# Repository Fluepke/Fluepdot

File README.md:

# Fluepdot

**Fluepdot** is a hardware and C project for controlling flip disc panels which where in use by the Berlin public transport operator **[BVG](https://www.bvg.de/en)**.

> This project was shown at [36C3](https://events.ccc.de/congress/2019/wiki/index.php/Main_Page). A large display was constructed from many flipdots. [Pictures](https://www.deutschlandfunkkultur.de/chaos-communication-congress-in-leipzig-auf-den-spuren-von.1264.de.html?dram:article_id=466775) [of](https://foto.benedikt-geyer.de/fluepdot-36c3/) [the](https://www.korrupt.biz/7204/36c3-nachtraege/) [installation](https://www.astrastudio.de/cloud/index.php/apps/gallery/s/nDda9j8dZQ2oNMy#IMG_7059.jpeg).

## Documentation
For **documentation** and a **getting started**, please head over to [https://fluepdot.readthedocs.io/en/latest/](https://fluepdot.readthedocs.io/en/latest/).

## Hardware

Flipdots and required HW  can be purchased by contacting [fluepdot-sales@luepke.email](mailto:fluepdot-sales@luepke.email).

## Firmware
You can download the latest standalone firmware installer [here](https://gitlab.com/fluepke/fluepdot/-/jobs/artifacts/master/raw/software/service_utility/service_utility?job=build_service_utility).

## License
Copyright (c) 2020, [@fluepke](http://twitter.com/fluepke) (Fabian Luepke)

Distributed under the terms of the GNU Affero General Public License version 3.

The full license is in the file LICENSE, distributed with this software.

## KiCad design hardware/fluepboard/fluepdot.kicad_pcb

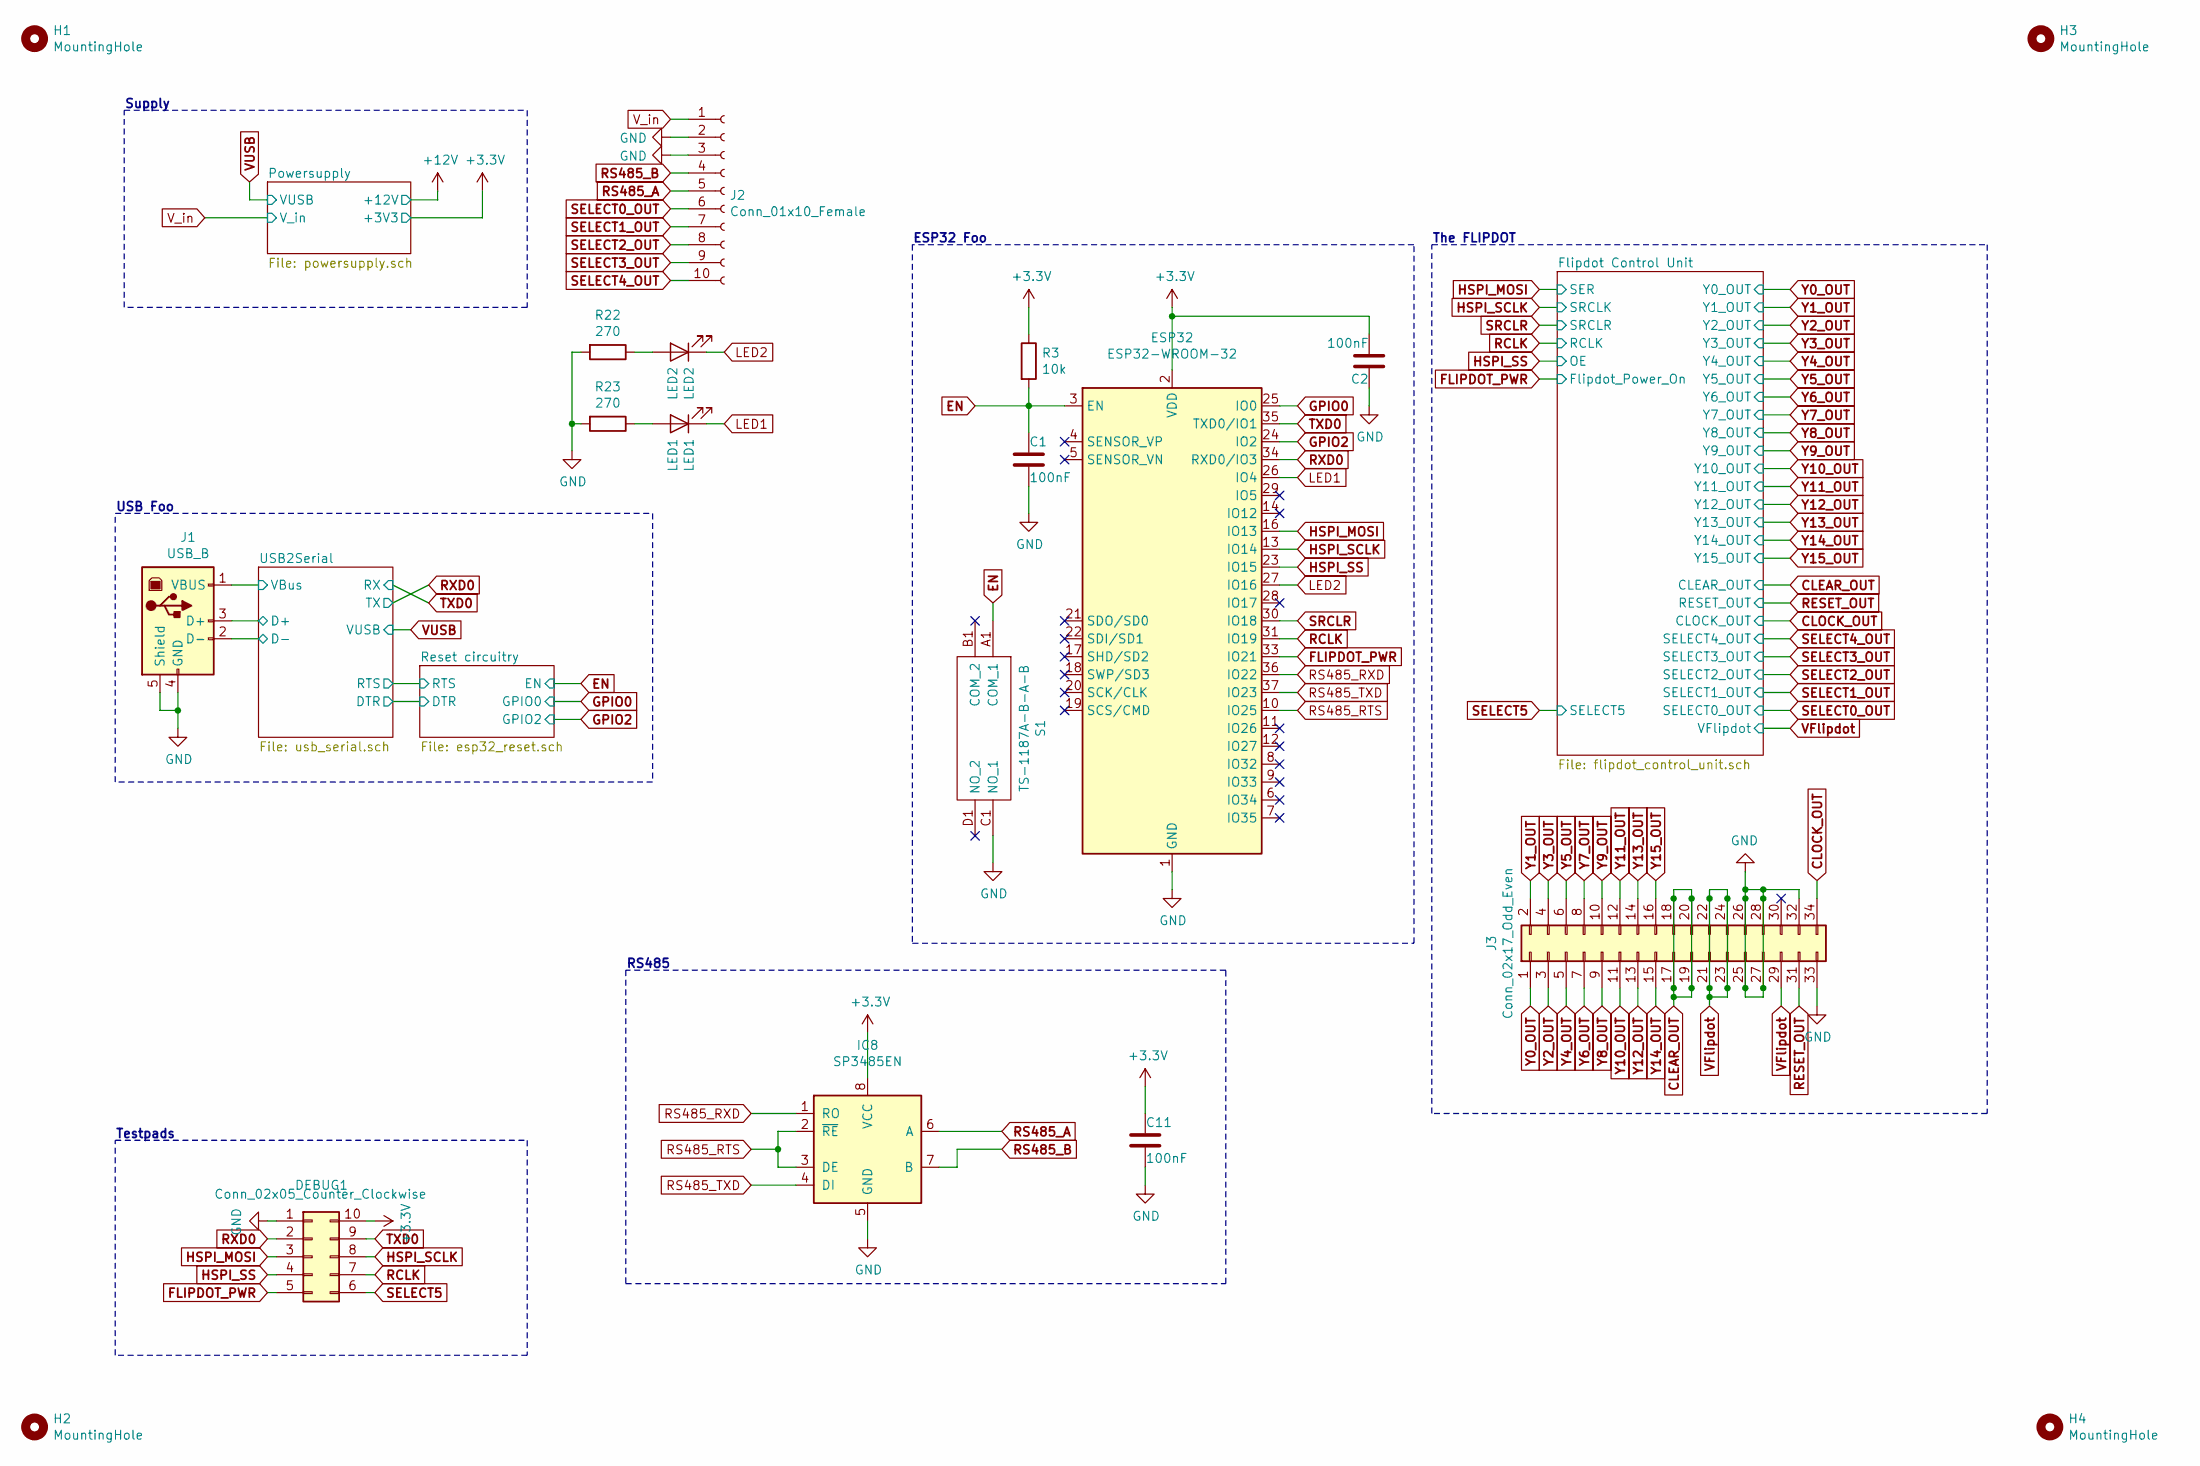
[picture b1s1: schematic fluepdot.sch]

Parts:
C1, C2, C11: 100nF; C_0603_1608Metric; LCSC C14663
DEBUG1: Conn_02x05_Counter_Clockwise; PinHeader_2x05_P2.54mm_Vertical
ESP32: ESP32-WROOM-32
H1, H2, H3, H4: MountingHole; MountingHole_3.2mm_M3_ISO7380
IC8: SP3485EN; SOIC-8_3.9x4.9mm_P1.27mm; LCSC C8963
J1: USB_B; USB_B_OST_USB-B1HSxx_Horizontal; LCSC C46392
J2: Conn_01x10_Female; TerminalBlock_Phoenix_MPT-0,5-10-2.54_1x10_P2.54mm_Horizont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
J3: Conn_02x17_Odd_Even; PinHeader_2x17_P2.54mm_Vertical
LED1: LED1; D_0805_2012Metric; LCSC C2296
LED2: LED2; D_0805_2012Metric; LCSC C2296
R3: 10k; R_0603_1608Metric; LCSC C25804
R22, R23: 270; R_0603_1608Metric; LCSC C22966
S1: TS-1187A-B-A-B; TS1187ABAB; Manufacturer_Part_Number TS-1187A-B-A-B; LCSC C318884

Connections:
+3V3: C2.2, C11.1, DEBUG1.10, ESP32.2 (VDD), IC8.8 (VCC), R3.1; also elsewhere on the board
/USB2Serial/D+: J1.3 (D+); also elsewhere on the board
/USB2Serial/D-: J1.2 (D-); also elsewhere on the board
/USB2Serial/VBus: J1.1 (VBUS); also elsewhere on the board
CLEAR_OUT: J3.17, J3.18, J3.19, J3.20; also elsewhere on the board
CLOCK_OUT: J3.34; also elsewhere on the board
EN: C1.1, ESP32.3 (EN), R3.2, S1.A1 (COM_1); also elsewhere on the board
FLIPDOT_PWR: DEBUG1.5, ESP32.33 (IO21); also elsewhere on the board
GND: C1.2, C2.1, C11.2, DEBUG1.1, ESP32.1 (GND), ESP32.15 (GND), ESP32.38 (GND), IC8.5 (GND), J1.4 (GND), J1.5 (Shield), J2.2, J2.3, J3.25, J3.26, J3.27, J3.28, J3.32, J3.33, R22.2, R23.2, S1.C1 (NO_1); also elsewhere on the board
GPIO0: ESP32.25 (IO0); also elsewhere on the board
GPIO2: ESP32.24 (IO2); also elsewhere on the board
HSPI_MOSI: DEBUG1.3, ESP32.16 (IO13); also elsewhere on the board
HSPI_SCLK: DEBUG1.8, ESP32.13 (IO14); also elsewhere on the board
HSPI_SS: DEBUG1.4, ESP32.23 (IO15); also elsewhere on the board
LED1: ESP32.26 (IO4), LED1.1 (K)
LED2: ESP32.27 (IO16), LED2.1 (K)
unnamed: LED1.2 (A), R23.1
unnamed: LED2.2 (A), R22.1
RCLK: DEBUG1.7, ESP32.31 (IO19); also elsewhere on the board
RESET_OUT: J3.31; also elsewhere on the board
RS485_A: IC8.6 (A), J2.5
RS485_B: IC8.7 (B), J2.4
RS485_RTS: ESP32.10 (IO25), IC8.2 (~RE~), IC8.3 (DE)
RS485_RXD: ESP32.36 (IO22), IC8.1 (RO)
RS485_TXD: ESP32.37 (IO23), IC8.4 (DI)
RXD0: DEBUG1.2, ESP32.34 (RXD0/IO3); also elsewhere on the board
SELECT0_OUT: J2.6; also elsewhere on the board
SELECT1_OUT: J2.7; also elsewhere on the board
SELECT2_OUT: J2.8; also elsewhere on the board
SELECT3_OUT: J2.9; also elsewhere on the board
SELECT4_OUT: J2.10; also elsewhere on the board
SELECT5: DEBUG1.6; also elsewhere on the board
SRCLR: ESP32.30 (IO18); also elsewhere on the board
TXD0: DEBUG1.9, ESP32.35 (TXD0/IO1); also elsewhere on the board
VFlipdot: J3.21, J3.22, J3.23, J3.24, J3.29; also elsewhere on the board
V_in: J2.1; also elsewhere on the board
Y0_OUT: J3.1; also elsewhere on the board
Y1_OUT: J3.2; also elsewhere on the board
Y2_OUT: J3.3; also elsewhere on the board
Y3_OUT: J3.4; also elsewhere on the board
Y4_OUT: J3.5; also elsewhere on the board
Y5_OUT: J3.6; also elsewhere on the board
Y6_OUT: J3.7; also elsewhere on the board
Y7_OUT: J3.8; also elsewhere on the board
Y8_OUT: J3.9; also elsewhere on the board
Y9_OUT: J3.10; also elsewhere on the board
Y10_OUT: J3.11; also elsewhere on the board
Y11_OUT: J3.12; also elsewhere on the board
Y12_OUT: J3.13; also elsewhere on the board
Y13_OUT: J3.14; also elsewhere on the board
Y14_OUT: J3.15; also elsewhere on the board
Y15_OUT: J3.16; also elsewhere on the board

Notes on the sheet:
Testpads
USB Foo
Supply
ESP32 Foo
The FLIPDOT
RS485

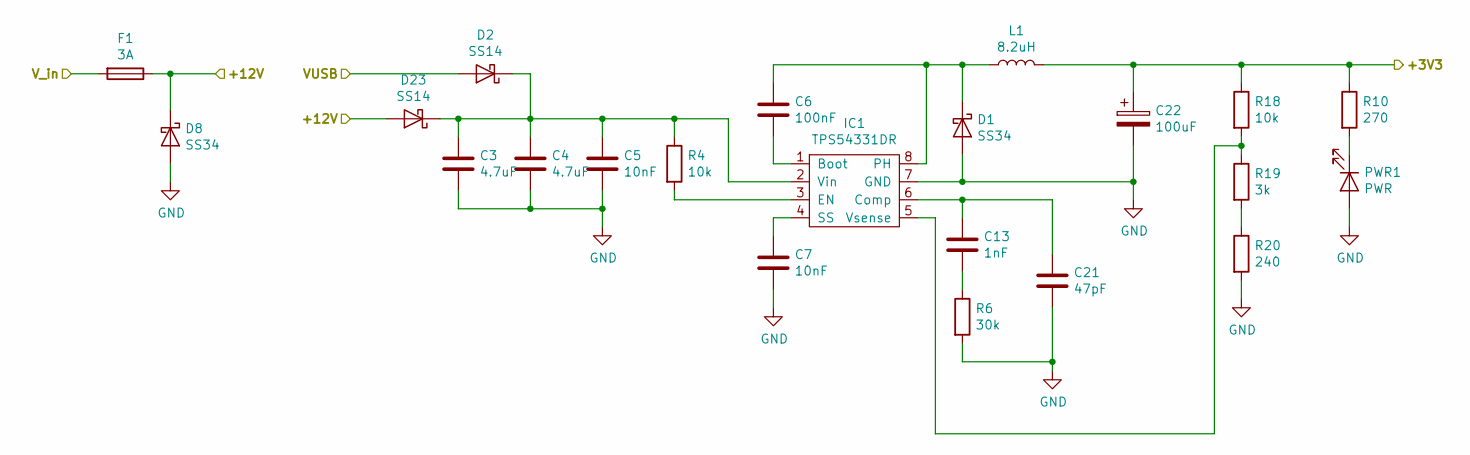
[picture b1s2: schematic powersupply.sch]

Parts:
C3, C4: 4.7uF; C_0805_2012Metric; LCSC C1779
C5, C7: 10nF; C_0603_1608Metric; LCSC C57112
C6: 100nF; C_0603_1608Metric; LCSC C14663
C13: 1nF; C_0603_1608Metric; LCSC C1588
C21: 47pF; C_0603_1608Metric; LCSC C1671
C22: 100uF; CP_EIA-3528-21_Kemet-B; LCSC C16133
D1, D8: SS34; D_SMA; LCSC C84635
D2, D23: SS14; D_SMA; LCSC C2480
F1: 3A; Fuse_1206_3216Metric; LCSC C182441
IC1: TPS54331DR; SOIC-8_3.9x4.9mm_P1.27mm; LCSC C9865
L1: 8.2uH; SMD-PIND-6.6x7.1x3.0_1.6x3.0; LCSC C132140
PWR1: PWR; D_0805_2012Metric; LCSC C2296
R4, R18: 10k; R_0603_1608Metric; LCSC C25804
R6: 30k; R_0603_1608Metric; LCSC C22984
R10: 270; R_0603_1608Metric; LCSC C22966
R19: 3k; R_0603_1608Metric; LCSC C4211
R20: 240; R_0603_1608Metric; LCSC C23350

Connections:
+3V3: C22.1, L1.2, R10.1, R18.1; also elsewhere on the board
+12V: D8.1 (K), D23.2 (A), F1.1; also elsewhere on the board
GND: C3.2, C4.2, C5.2, C7.2, C21.2, C22.2, D1.2 (A), D8.2 (A), IC1.7 (GND), PWR1.2 (A), R6.2, R20.2; also elsewhere on the board
unnamed: C3.1, C4.1, C5.1, D2.1 (K), D23.1 (K), IC1.2 (Vin), R4.1
unnamed: C6.1, D1.1 (K), IC1.8 (PH), L1.1
unnamed: C6.2, IC1.1 (Boot)
unnamed: C7.1, IC1.4 (SS)
unnamed: C13.1, C21.1, IC1.6 (Comp)
unnamed: C13.2, R6.1
unnamed: IC1.3 (EN), R4.2
unnamed: IC1.5 (Vsense), R18.2, R19.1
unnamed: PWR1.1 (K), R10.2
unnamed: R19.2, R20.1
VUSB: D2.2 (A); also elsewhere on the board
V_in: F1.2; also elsewhere on the board

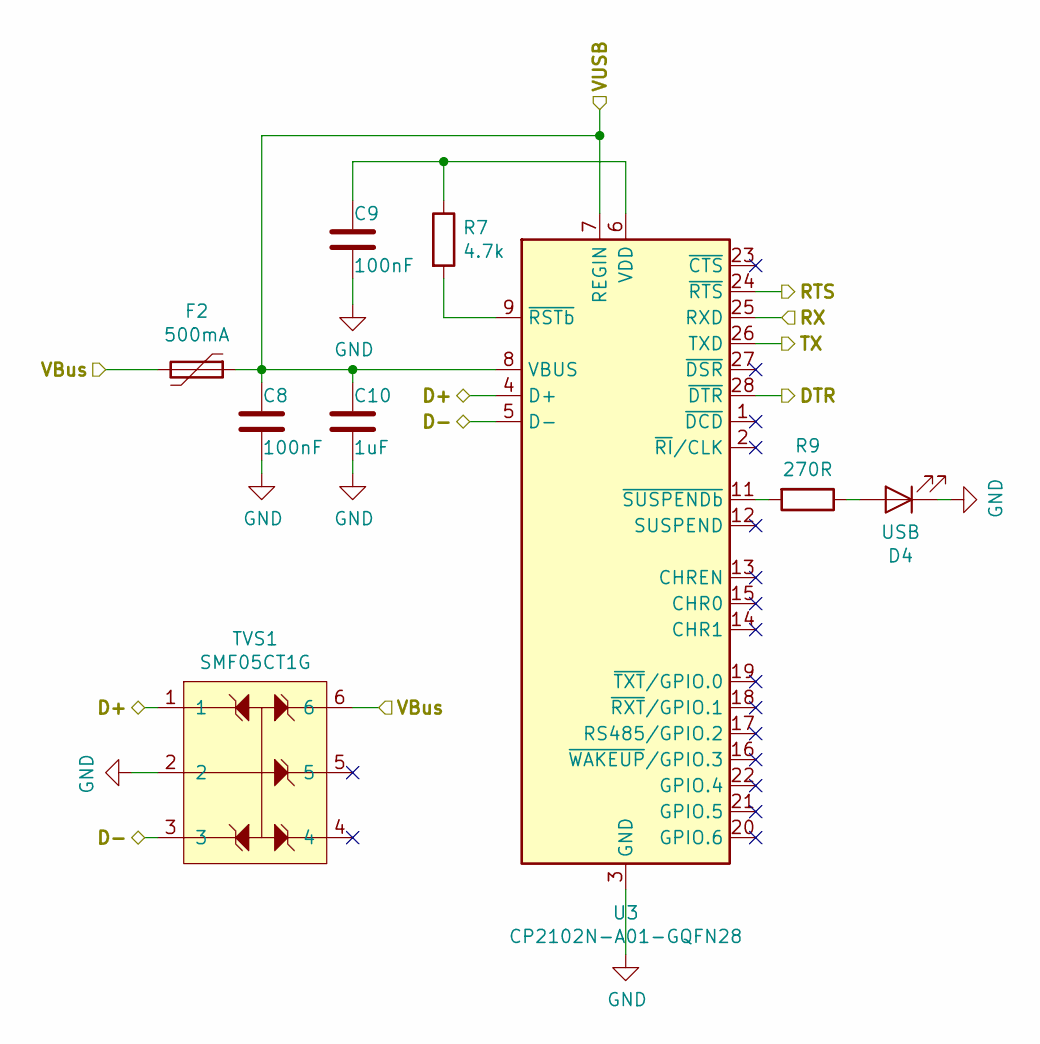
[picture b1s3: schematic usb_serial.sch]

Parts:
C8, C9: 100nF; C_0603_1608Metric; LCSC C14663
C10: 1uF; C_0603_1608Metric; LCSC C15849
D4: USB; D_0805_2012Metric; LCSC C2296
F2: 500mA; Fuse_1206_3216Metric; LCSC C69688
R7: 4.7k; R_0603_1608Metric; LCSC C23162
R9: 270R; R_0603_1608Metric; LCSC C22966
TVS1: SMF05CT1G; SOT-363_SC-70-6; LCSC C15879
U3: CP2102N-A01-GQFN28; QFN-28-1EP_5x5mm_P0.5mm_EP3.35x3.35mm; LCSC C6568

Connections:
/Reset circuitry/DTR: U3.28 (~DTR); also elsewhere on the board
/Reset circuitry/RTS: U3.24 (~RTS); also elsewhere on the board
/USB2Serial/D+: TVS1.1, U3.4 (D+); also elsewhere on the board
/USB2Serial/D-: TVS1.3, U3.5 (D-); also elsewhere on the board
/USB2Serial/VBus: F2.2, TVS1.6; also elsewhere on the board
GND: C8.1, C9.1, C10.1, D4.1 (K), TVS1.2, U3.3 (GND), U3.29 (GND); also elsewhere on the board
unnamed: C9.2, R7.1, U3.6 (VDD)
unnamed: D4.2 (A), R9.1
unnamed: R7.2, U3.9 (~RSTb)
unnamed: R9.2, U3.11 (~SUSPENDb)
RXD0: U3.26 (TXD); also elsewhere on the board
TXD0: U3.25 (RXD); also elsewhere on the board
VUSB: C8.2, C10.2, F2.1, U3.7 (REGIN), U3.8 (VBUS); also elsewhere on the board

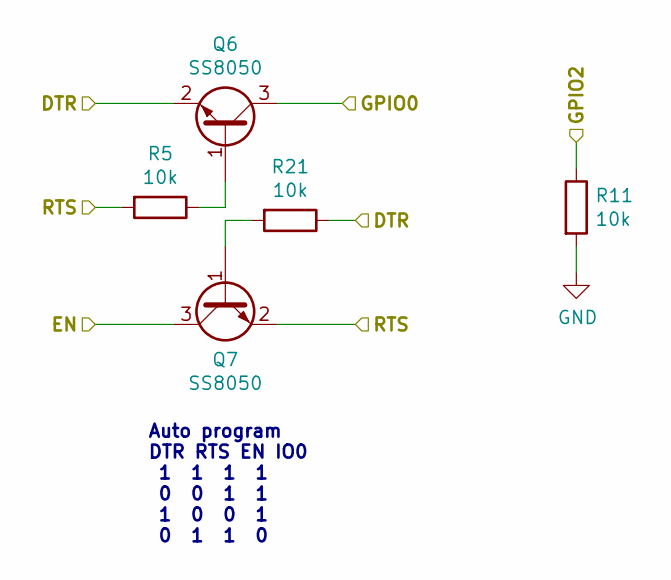
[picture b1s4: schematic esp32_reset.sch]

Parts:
Q6, Q7: SS8050; SOT-23; LCSC C2150
R5, R11, R21: 10k; R_0603_1608Metric; LCSC C25804

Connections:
/Reset circuitry/DTR: Q6.2 (E), R21.1; also elsewhere on the board
/Reset circuitry/RTS: Q7.2 (E), R5.2; also elsewhere on the board
EN: Q7.3 (C); also elsewhere on the board
GND: R11.2; also elsewhere on the board
GPIO0: Q6.3 (C); also elsewhere on the board
GPIO2: R11.1; also elsewhere on the board
unnamed: Q6.1 (B), R5.1
unnamed: Q7.1 (B), R21.2

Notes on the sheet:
Auto program DTR RTS EN IO0 1 1 1 1 0 0 1 1 1 0 0 1 0 1 1 0

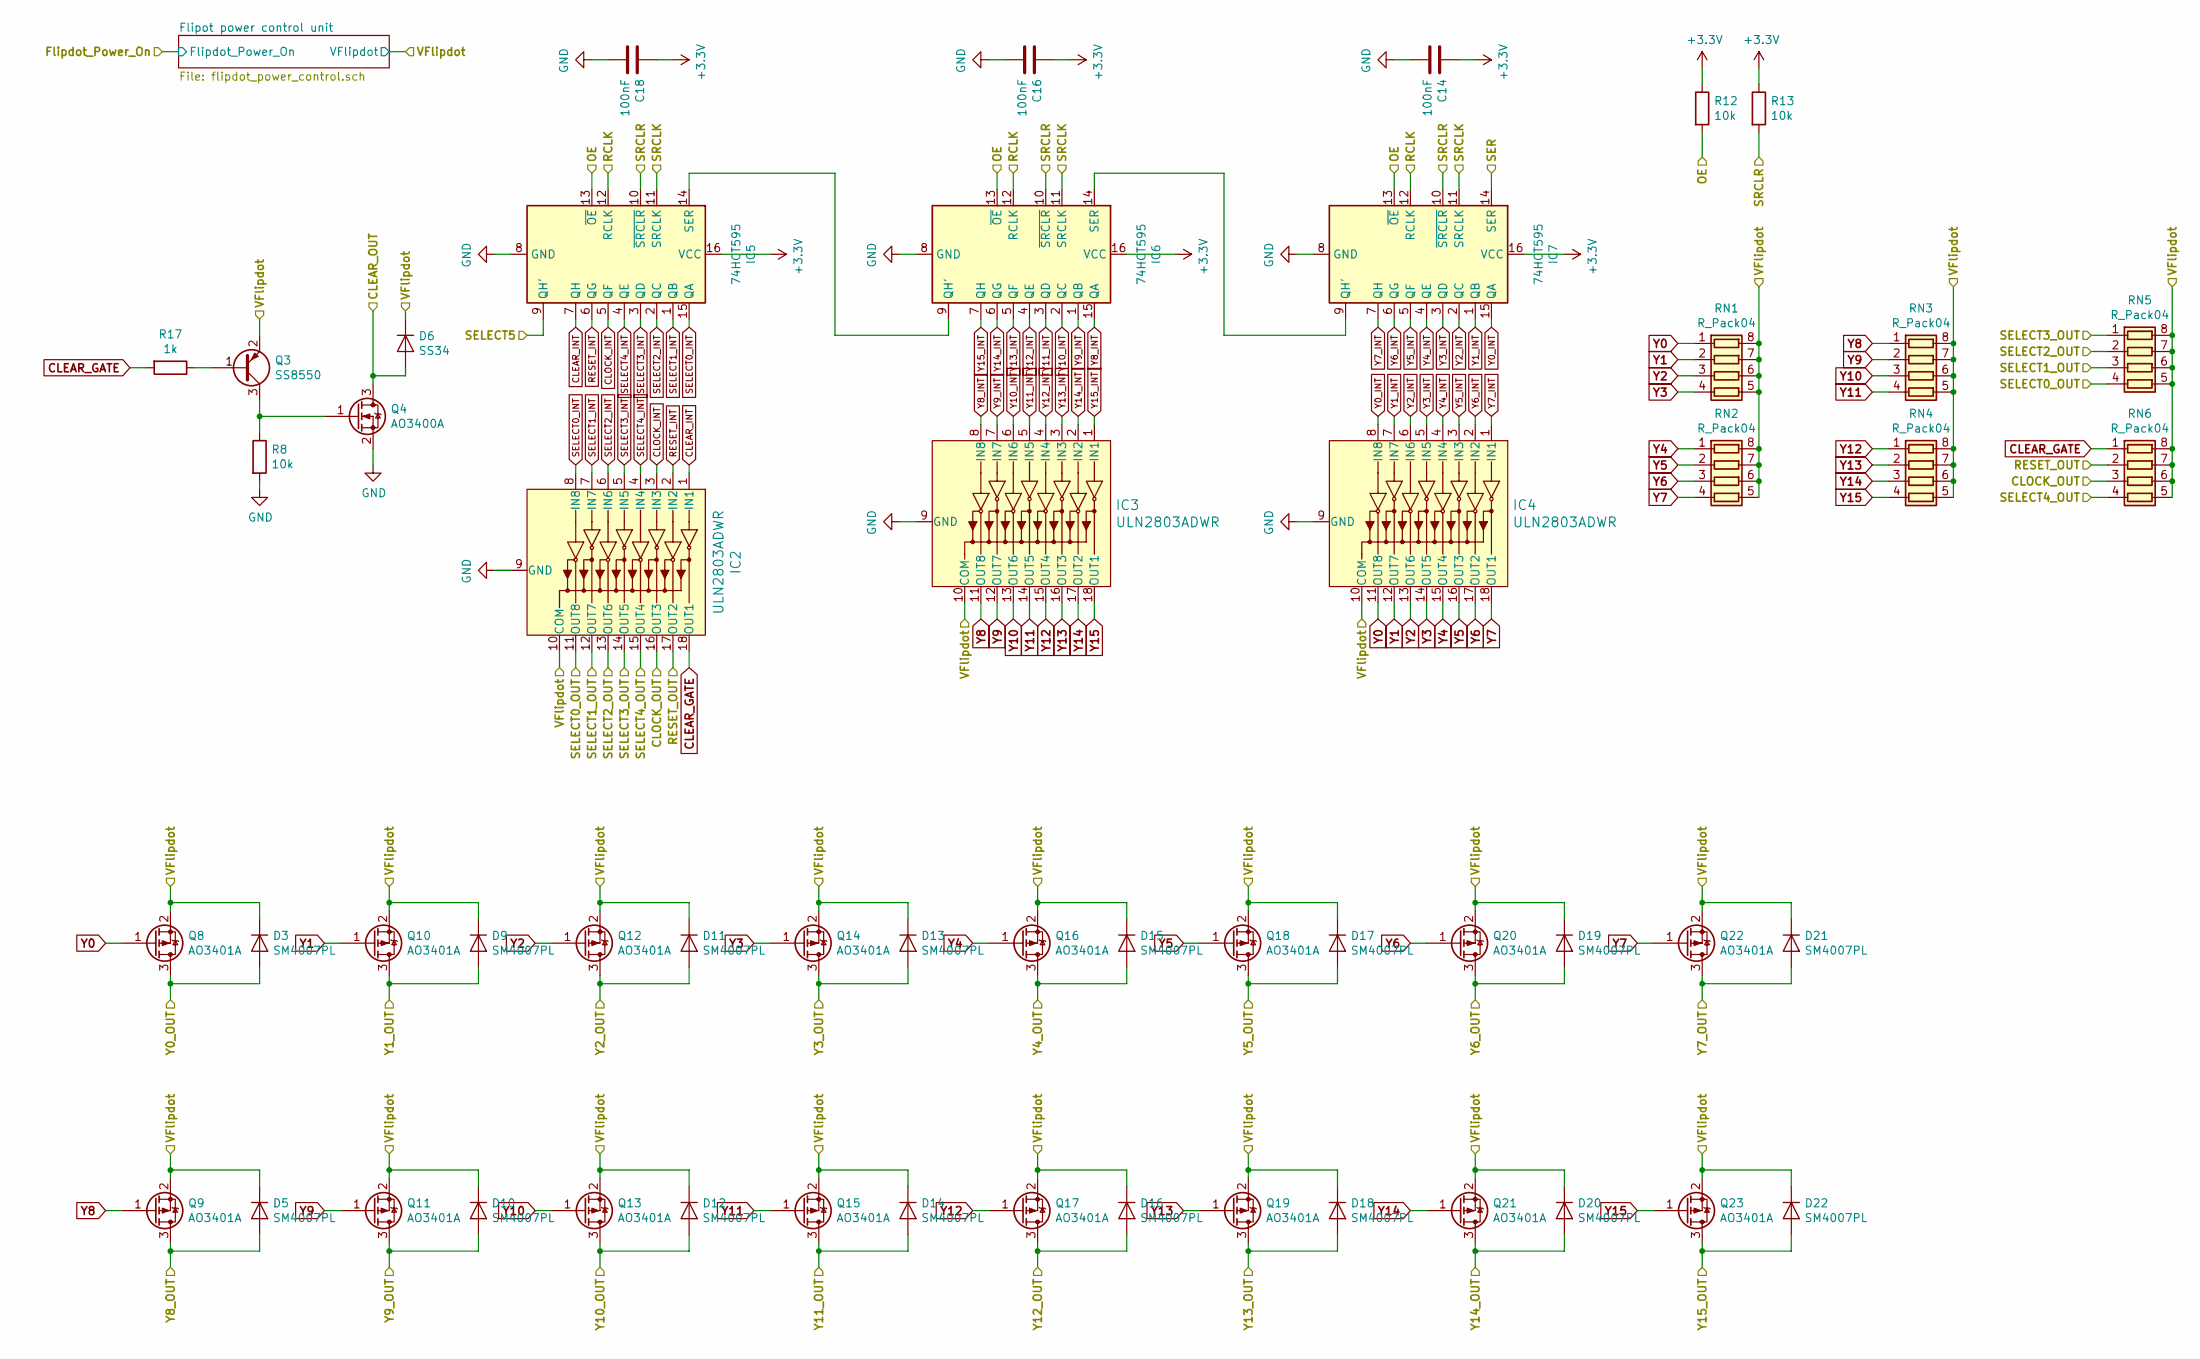
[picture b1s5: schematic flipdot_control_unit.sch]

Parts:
C14, C16, C18: 100nF; C_0603_1608Metric; LCSC C14663
D3, D5, D9, D10, D11, D12, D13, D14, D15, D16, D17, D18, D19, D20, D21, D22: SM4007PL; D_SOD-123F; LCSC C64898
D6: SS34; D_SMA; LCSC C84635
IC2, IC3, IC4: ULN2803ADWR; SOIC-18W_7.5x11.6mm_P1.27mm; MPN ULN2803ADWR; Digi-Key_PN 296-15777-1-ND
IC5, IC6, IC7: 74HCT595; SOIC-16_3.9x9.9mm_P1.27mm; LCSC C5613
Q3: SS8550; SOT-23; LCSC C8542
Q4: AO3400A; SOT-23; LCSC C20917
Q8, Q9, Q10, Q11, Q12, Q13, Q14, Q15, Q16, Q17, Q18, Q19, Q20, Q21, Q22, Q23: AO3401A; SOT-23; LCSC C15127
R8, R12, R13: 10k; R_0603_1608Metric; LCSC C25804
R17: 1k; R_0603_1608Metric; LCSC C21190
RN1, RN2, RN3, RN4, RN5, RN6: R_Pack04; R_Array_Convex_4x0603; LCSC C29718

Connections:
+3V3: C14.1, C16.1, C18.1, IC5.16 (VCC), IC6.16 (VCC), IC7.16 (VCC), R12.1, R13.1; also elsewhere on the board
CLEAR_GATE: IC2.18 (OUT1), R17.2, RN6.1 (R1.1)
CLEAR_INT: IC2.1 (IN1), IC5.7 (QH)
CLEAR_OUT: D6.2 (A), Q4.3 (D); also elsewhere on the board
CLOCK_INT: IC2.3 (IN3), IC5.5 (QF)
CLOCK_OUT: IC2.16 (OUT3), RN6.3 (R3.1); also elsewhere on the board
GND: C14.2, C16.2, C18.2, IC2.9 (GND), IC3.9 (GND), IC4.9 (GND), IC5.8 (GND), IC6.8 (GND), IC7.8 (GND), Q4.2 (S), R8.2; also elsewhere on the board
HSPI_MOSI: IC7.14 (SER); also elsewhere on the board
HSPI_SCLK: IC5.11 (SRCLK), IC6.11 (SRCLK), IC7.11 (SRCLK); also elsewhere on the board
HSPI_SS: IC5.13 (~OE), IC6.13 (~OE), IC7.13 (~OE), R12.2; also elsewhere on the board
unnamed: IC5.14 (SER), IC6.9 (QH')
unnamed: IC6.14 (SER), IC7.9 (QH')
unnamed: Q3.1 (B), R17.1
unnamed: Q3.3 (C), Q4.1 (G), R8.1
RCLK: IC5.12 (RCLK), IC6.12 (RCLK), IC7.12 (RCLK); also elsewhere on the board
RESET_INT: IC2.2 (IN2), IC5.6 (QG)
RESET_OUT: IC2.17 (OUT2), RN6.2 (R2.1); also elsewhere on the board
SELECT0_INT: IC2.8 (IN8), IC5.15 (QA)
SELECT0_OUT: IC2.11 (OUT8), RN5.4 (R4.1); also elsewhere on the board
SELECT1_INT: IC2.7 (IN7), IC5.1 (QB)
SELECT1_OUT: IC2.12 (OUT7), RN5.3 (R3.1); also elsewhere on the board
SELECT2_INT: IC2.6 (IN6), IC5.2 (QC)
SELECT2_OUT: IC2.13 (OUT6), RN5.2 (R2.1); also elsewhere on the board
SELECT3_INT: IC2.5 (IN5), IC5.3 (QD)
SELECT3_OUT: IC2.14 (OUT5), RN5.1 (R1.1); also elsewhere on the board
SELECT4_INT: IC2.4 (IN4), IC5.4 (QE)
SELECT4_OUT: IC2.15 (OUT4), RN6.4 (R4.1); also elsewhere on the board
SELECT5: IC5.9 (QH'); also elsewhere on the board
SRCLR: IC5.10 (~SRCLR), IC6.10 (~SRCLR), IC7.10 (~SRCLR), R13.2; also elsewhere on the board
VFlipdot: D3.1 (K), D5.1 (K), D6.1 (K), D9.1 (K), D10.1 (K), D11.1 (K), D12.1 (K), D13.1 (K), D14.1 (K), D15.1 (K), D16.1 (K), D17.1 (K), D18.1 (K), D19.1 (K), D20.1 (K), D21.1 (K), D22.1 (K), IC2.10 (COM), IC3.10 (COM), IC4.10 (COM), Q3.2 (E), Q8.2 (S), Q9.2 (S), Q10.2 (S), Q11.2 (S), Q12.2 (S), Q13.2 (S), Q14.2 (S), Q15.2 (S), Q16.2 (S), Q17.2 (S), Q18.2 (S), Q19.2 (S), Q20.2 (S), Q21.2 (S), Q22.2 (S), Q23.2 (S), RN1.5 (R4.2), RN1.6 (R3.2), RN1.7 (R2.2), RN1.8 (R1.2), RN2.5 (R4.2), RN2.6 (R3.2), RN2.7 (R2.2), RN2.8 (R1.2), RN3.5 (R4.2), RN3.6 (R3.2), RN3.7 (R2.2), RN3.8 (R1.2), RN4.5 (R4.2), RN4.6 (R3.2), RN4.7 (R2.2), RN4.8 (R1.2), RN5.5 (R4.2), RN5.6 (R3.2), RN5.7 (R2.2), RN5.8 (R1.2), RN6.5 (R4.2), RN6.6 (R3.2), RN6.7 (R2.2), RN6.8 (R1.2); also elsewhere on the board
Y0: IC4.11 (OUT8), Q8.1 (G), RN1.1 (R1.1)
Y0_INT: IC4.8 (IN8), IC7.15 (QA)
Y0_OUT: D3.2 (A), Q8.3 (D); also elsewhere on the board
Y1: IC4.12 (OUT7), Q10.1 (G), RN1.2 (R2.1)
Y1_INT: IC4.7 (IN7), IC7.1 (QB)
Y1_OUT: D9.2 (A), Q10.3 (D); also elsewhere on the board
Y2: IC4.13 (OUT6), Q12.1 (G), RN1.3 (R3.1)
Y2_INT: IC4.6 (IN6), IC7.2 (QC)
Y2_OUT: D11.2 (A), Q12.3 (D); also elsewhere on the board
Y3: IC4.14 (OUT5), Q14.1 (G), RN1.4 (R4.1)
Y3_INT: IC4.5 (IN5), IC7.3 (QD)
Y3_OUT: D13.2 (A), Q14.3 (D); also elsewhere on the board
Y4: IC4.15 (OUT4), Q16.1 (G), RN2.1 (R1.1)
Y4_INT: IC4.4 (IN4), IC7.4 (QE)
Y4_OUT: D15.2 (A), Q16.3 (D); also elsewhere on the board
Y5: IC4.16 (OUT3), Q18.1 (G), RN2.2 (R2.1)
Y5_INT: IC4.3 (IN3), IC7.5 (QF)
Y5_OUT: D17.2 (A), Q18.3 (D); also elsewhere on the board
Y6: IC4.17 (OUT2), Q20.1 (G), RN2.3 (R3.1)
Y6_INT: IC4.2 (IN2), IC7.6 (QG)
Y6_OUT: D19.2 (A), Q20.3 (D); also elsewhere on the board
Y7: IC4.18 (OUT1), Q22.1 (G), RN2.4 (R4.1)
Y7_INT: IC4.1 (IN1), IC7.7 (QH)
Y7_OUT: D21.2 (A), Q22.3 (D); also elsewhere on the board
Y8: IC3.11 (OUT8), Q9.1 (G), RN3.1 (R1.1)
Y8_INT: IC3.8 (IN8), IC6.15 (QA)
Y8_OUT: D5.2 (A), Q9.3 (D); also elsewhere on the board
Y9: IC3.12 (OUT7), Q11.1 (G), RN3.2 (R2.1)
Y9_INT: IC3.7 (IN7), IC6.1 (QB)
Y9_OUT: D10.2 (A), Q11.3 (D); also elsewhere on the board
Y10: IC3.13 (OUT6), Q13.1 (G), RN3.3 (R3.1)
Y10_INT: IC3.6 (IN6), IC6.2 (QC)
Y10_OUT: D12.2 (A), Q13.3 (D); also elsewhere on the board
Y11: IC3.14 (OUT5), Q15.1 (G), RN3.4 (R4.1)
Y11_INT: IC3.5 (IN5), IC6.3 (QD)
Y11_OUT: D14.2 (A), Q15.3 (D); also elsewhere on the board
Y12: IC3.15 (OUT4), Q17.1 (G), RN4.1 (R1.1)
Y12_INT: IC3.4 (IN4), IC6.4 (QE)
Y12_OUT: D16.2 (A), Q17.3 (D); also elsewhere on the board
Y13: IC3.16 (OUT3), Q19.1 (G), RN4.2 (R2.1)
Y13_INT: IC3.3 (IN3), IC6.5 (QF)
Y13_OUT: D18.2 (A), Q19.3 (D); also elsewhere on the board
Y14: IC3.17 (OUT2), Q21.1 (G), RN4.3 (R3.1)
Y14_INT: IC3.2 (IN2), IC6.6 (QG)
Y14_OUT: D20.2 (A), Q21.3 (D); also elsewhere on the board
Y15: IC3.18 (OUT1), Q23.1 (G), RN4.4 (R4.1)
Y15_INT: IC3.1 (IN1), IC6.7 (QH)
Y15_OUT: D22.2 (A), Q23.3 (D); also elsewhere on the board

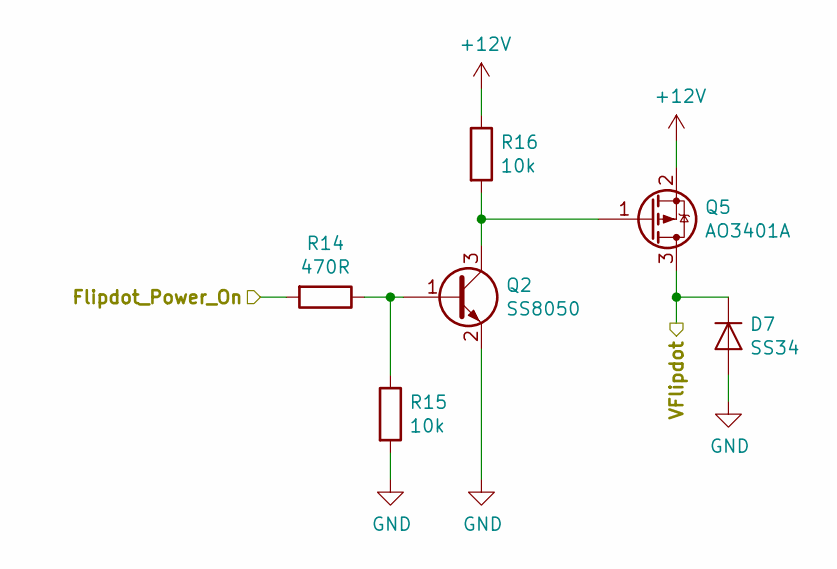
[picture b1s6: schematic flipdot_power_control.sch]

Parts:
D7: SS34; D_SMA; LCSC C84635
Q2: SS8050; SOT-23; LCSC C2150
Q5: AO3401A; SOT-23; LCSC C15127
R14: 470R; R_0603_1608Metric; LCSC C23179
R15, R16: 10k; R_0603_1608Metric; LCSC C25804

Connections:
+12V: Q5.2 (S), R16.1; also elsewhere on the board
FLIPDOT_PWR: R14.2; also elsewhere on the board
GND: D7.2 (A), Q2.2 (E), R15.2; also elsewhere on the board
unnamed: Q2.1 (B), R14.1, R15.1
unnamed: Q2.3 (C), Q5.1 (G), R16.2
VFlipdot: D7.1 (K), Q5.3 (D); also elsewhere on the board

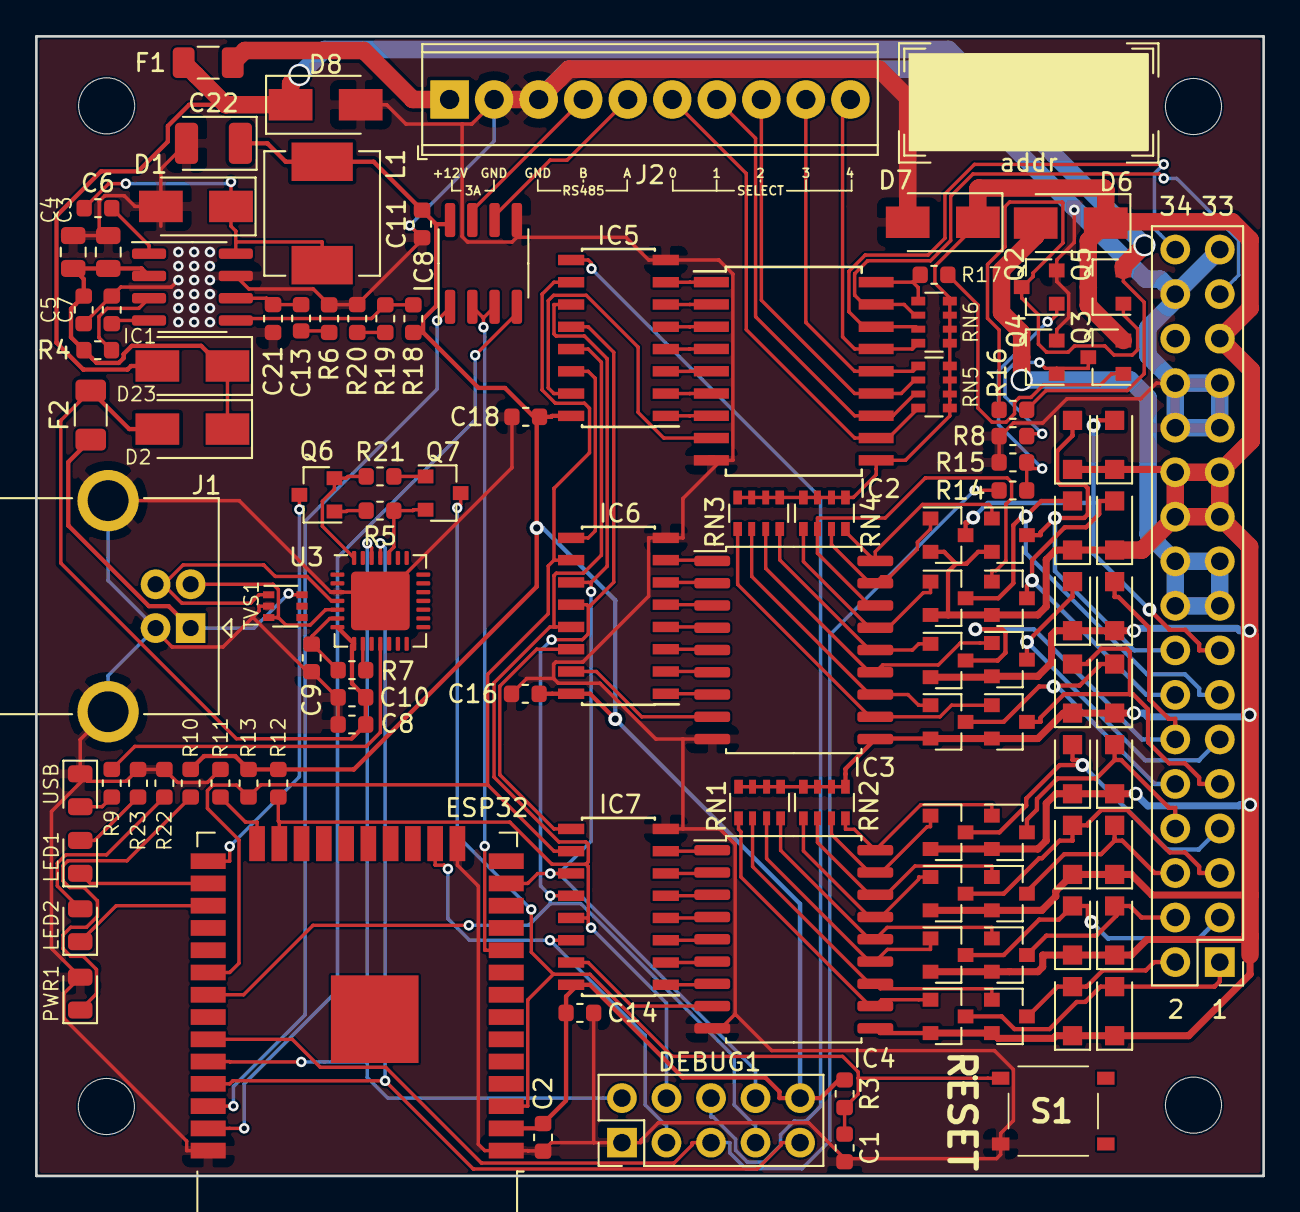
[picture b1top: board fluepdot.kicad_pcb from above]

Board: 2 copper layers, 70.0 x 65.0 mm, 115 parts (0 on the bottom side), 119 nets.

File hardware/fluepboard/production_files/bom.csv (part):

Comment,Designator,Footprint,LCSC, LCSC, Octopart, Description, Extended Part, Manufacturer, Height, LCSC Price/Stock, Manufacturer_Name, Manufacturer_Part_Number, Category, DK_Datasheet_Link, DK_Detail_Page, Digi-Key_PN, Family, MPN, status, Status
"100nF","C1,C2,C11,C6,C9,C8,C18,C16,C14","Capacitor_SMD:C_0603_1608Metric","","C14663","C0805C104Z5VACTU","MULTILAYER CERAMIC CAPACITORS MLCC - SMD/SMT 100NF 50V 0603 ROHS","0","CC0603KRX7R9BB104","","","","","","","","","","","",""
"1uF","C10","Capacitor_SMD:C_0603_1608Metric","","C15849","","MULTILAYER CERAMIC CAPACITORS MLCC - SMD/SMT 1UF 50V 0603 ROHS","0","CL10A105KB8NNNC","","","","","","","","","","","",""
"1nF","C13","Capacitor_SMD:C_0603_1608Metric","","C1588","","MULTILAYER CERAMIC CAPACITORS MLCC - SMD/SMT 1NF 50V 0603 ROHS","0","CL10B102KB8NNNC","","","","","","","","","","","",""
"47pF","C21","Capacitor_SMD:C_0603_1608Metric","","C1671","","MULTILAYER CERAMIC CAPACITORS MLCC - SMD/SMT 47PF 50V 0603 ROHS","0","CL10C470JB8NNNC","","","","","","","","","","","",""
"100uF","C22","Capacitor_Tantalum_SMD:CP_EIA-3528-21_Kemet-B","","C16133","","TANTALUM CAPACITORS 100UF 6.3V CASE-B_3528 ROHS","0","TAJB107K006RNJ","","","","","","","","","","","",""
"4.7uF","C4,C3","Capacitor_SMD:C_0805_2012Metric","","C1779","","MULTILAYER CERAMIC CAPACITORS MLCC - SMD/SMT 4.7UF 25V 0805 ROHS","0","CL21A475KAQNNNE","","","","","","","","","","","",""
"10nF","C5,C7","Capacitor_SMD:C_0603_1608Metric","","C57112","","MULTILAYER CERAMIC CAPACITORS MLCC - SMD/SMT 10NF 50V 0603 ROHS","0","0603B103K500NT","","","","","","","","","","","",""
"SS14","D2,D23","Diode_SMD:D_SMA","","C2480","","SCHOTTKY BARRIER DIODES (SBD) SMA(DO-214AC) ROHS","0","SS14","","","","","","","","","","","",""
"SM4007PL","D3,D9,D11,D13,D15,D17,D19,D21,D5,D10,D12,D14,D16,D18,D20,D22","Diode_SMD:D_SOD-123F","","C64898","","","","SM4007PL","","","","","","","","","","","",""
"USB","D4","Diode_SMD:D_0805_2012Metric","","C2296","SML-211YTT86","LIGHT EMITTING DIODES (LED) YELLOW 592~594NM 95~113MCD@20MA TOP VIEW 0805 ROHS","0","17-21SUYC/TR8","","","","","","","","","","","",""
"SS34","D8,D1,D6,D7","Diode_SMD:D_SMA","","C84635","B140-E3/61T","SCHOTTKY BARRIER DIODES (SBD) SMA(DO-214AC) ROHS","0","SS34","","","","","","","","","","","",""
"Conn_02x05_Counter_Clockwise","DEBUG1","Connector_PinHeader_2.54mm:PinHeader_2x05_P2.54mm_Vertical","","","Molex 10-89-7101","","","","","","","","","","","","","","",""
"ESP32-WROOM-32","ESP32","RF_Module:ESP32-WROOM-32","","-","ESP32-WROOM-32","","","","","","","","","","","","","","",""
"3A","F1","Fuse:Fuse_1206_3216Metric","","C182441","","SURFACE MOUNT FUSES 1206 ROHS","1","12D1300C","","","","","","","","","","","",""
"500mA","F2","Fuse:Fuse_1206_3216Metric","","C69688","3413.0113.22","PTC RESETTABLE FUSES 1206 ROHS","1","nSMD050","","","","","","","","","","","",""
"MountingHole","H1,H3,H4,H2","MountingHole:MountingHole_3.2mm_M3_ISO7380",""
"TPS54331DR","IC1","Package_SO:SOIC-8_3.9x4.9mm_P1.27mm","","C9865","","DC-DC CONVERTERS STEP-DOWN ADJUSTABLE 1 3.5V 28V 0.8V 25V 3A SOIC-8_150MIL ROHS","0","TPS54331DR","","","","","","","","","","","",""
"ULN2803ADWR","IC2,IC4,IC3","Package_SO:SOIC-18W_7.5x11.6mm_P1.27mm","","C9683","ULN2803ADW","TRANS 8NPN DARL 50V 0.5A 18SO","0","ULN2803ADWR","","","","","Discrete Semiconductor Products","http://www.ti.com/lit/ds/symlink/uln2803a.pdf","/product-detail/en/texas-instruments/ULN2803ADWR/296-15777-1-ND/598088","296-15777-1-ND","Transistors - Bipolar (BJT) - Arrays","ULN2803ADWR","review",""
"74HCT595","IC7,IC6,IC5","Package_SO:SOIC-16_3.9x9.9mm_P1.27mm","","C5613","MC74HC595ADG","","0","","","","","","","","","","","","",""
"SP3485EN","IC8","Package_SO:SOIC-8_3.9x4.9mm_P1.27mm","","C8963","","","0","CP2102-GMR","","","","","","","","","","","",""
"USB_B","J1","Connector_USB:USB_B_OST_USB-B1HSxx_Horizontal","","C46392","","","","","","","","","","","","","","","",""
"Conn_01x10_Female","J2","fluepdot:TerminalBlock_Phoenix_MPT-0,5-10-2.54_1x10_P2.54mm_Horizontal",""
"Conn_02x17_Odd_Even","J3","Connector_PinHeader_2.54mm:PinHeader_2x17_P2.54mm_Vertical","","","XG4A-3431","","","","","","","","","","","","","","",""
"8.2uH","L1","fluepdot:SMD-PIND-6.6x7.1x3.0_1.6x3.0","","C132140","","POWER INDUCTORS 8.2UH ±20% 5A SMD,6.6X7.1X3.0MM ROHS","1","MWSA0603-8R2MT","","","","","","","","","","","",""
"LED1","LED1","Diode_SMD:D_0805_2012Metric","","C2296","","LIGHT EMITTING DIODES (LED) YELLOW 592~594NM 95~113MCD@20MA TOP VIEW 0805 ROHS","0","17-21SUYC/TR8","","","","","","","","","","","",""
"LED2","LED2","Diode_SMD:D_0805_2012Metric","","C2296","","LIGHT EMITTING DIODES (LED) YELLOW 592~594NM 95~113MCD@20MA TOP VIEW 0805 ROHS","0","17-21SUYC/TR8","","","","","","","","","","","",""
"PWR","PWR1","Diode_SMD:D_0805_2012Metric","","C2296","","LIGHT EMITTING DIODES (LED) YELLOW 592~594NM 95~113MCD@20MA TOP VIEW 0805 ROHS","0","17-21SUYC/TR8","","","","","","","","","","","",""
"SS8550","Q3","Package_TO_SOT_SMD:SOT-23","","C8542","","TRANSISTORS (NPN/PNP) PNP 1.5A 25V SOT-23(SOT-23-3) ROHS","0","SS8550","","","","","","","","","","","",""
"AO3400A","Q4","Package_TO_SOT_SMD:SOT-23","","C20917","","MOSFET N TRENCH 30V 5.7A 1.5V @ 250UA 26.5 M? @ 5.7A,10V SOT-23-3L ROHS","0","AO3400A","","","","","","","","","","","",""
"SS8050","Q6,Q7,Q2","Package_TO_SOT_SMD:SOT-23","","C2150","","TRANSISTORS (NPN/PNP) NPN 1.5A 25V SOT-23(SOT-23-3) ROHS","0","","","","","","","","","","","","",""
"AO3401A","Q8,Q10,Q12,Q14,Q16,Q18,Q20,Q22,Q9,Q11,Q13,Q15,Q17,Q19,Q21,Q23,Q5","Package_TO_SOT_SMD:SOT-23","","C15127","","MOSFET P TRENCH 30V 4A 1.3V @ 250UA 44 M? @ 4.3A,10V SOT-23-3L ROHS","0","AO3401A","","","","","","","","","","","",""
"470R","R14","Resistor_SMD:R_0603_1608Metric","","C23179","RC0805FR-07470RL","CHIP RESISTOR - SURFACE MOUNT 470OHMS ±1% 1/10W 0603 ROHS","0","0603WAF4700T5E","","","","","","","","","","","",""
"1k","R17","Resistor_SMD:R_0603_1608Metric","","C21190","RC0805FR-071K","CHIP RESISTOR - SURFACE MOUNT 1KOHMS ±1% 1/10W 0603 ROHS","0","0603WAF1001T5E","","","","","","","","","","","",""
"3k","R19","Resistor_SMD:R_0603_1608Metric","","C4211","","CHIP RESISTOR - SURFACE MOUNT 3KOHMS ±1% 1/10W 0603 ROHS","0","0603WAF3001T5E","","","","","","","","","","","",""
"240","R20","Resistor_SMD:R_0603_1608Metric","","C23350","","CHIP RESISTOR - SURFACE MOUNT 240OHMS ±1% 1/10W 0603 ROHS","0","0603WAF2400T5E","","","","","","","","","","","",""
"270","R23,R22,R10","Resistor_SMD:R_0603_1608Metric","","C22966","","CHIP RESISTOR - SURFACE MOUNT 270OHMS ±1% 1/10W 0603 ROHS","0","0603WAF2700T5E","","","","","","","","","","","",""
"10k","R3,R4,R18,R11,R5,R21,R12,R13,R8,R16,R15","Resistor_SMD:R_0603_1608Metric","","C25804","RC0805FR-0710KL","CHIP RESISTOR - SURFACE MOUNT 10KOHMS ±1% 1/10W 0603 ROHS","0","0603WAF1002T5E","","","","","","","","","","","",""
"30k","R6","Resistor_SMD:R_0603_1608Metric","","C22984","","CHIP RESISTOR - SURFACE MOUNT 30KOHMS ±1% 1/10W 0603 ROHS","0","0603WAF1002T5E","","","","","","","","","","","",""
"4.7k","R7","Resistor_SMD:R_0603_1608Metric","","C23162","","CHIP RESISTOR - SURFACE MOUNT 4.7KOHMS ±1% 1/10W 0603 ROHS","0","0603WAF4701T5E","","","","","","","","","","","",""
"270R","R9","Resistor_SMD:R_0603_1608Metric","","C22966","RC0805FR-07270RL","CHIP RESISTOR - SURFACE MOUNT 270OHMS ±1% 1/10W 0603 ROHS","0","0603WAF2700T5E","","","","","","","","","","","",""
"R_Pack04","RN5,RN6,RN1,RN2,RN3,RN4","Resistor_SMD:R_Array_Convex_4x0603","","C29718","","RESISTOR NETWORKS & ARRAYS 10KOHMS ±5% 1/16W 0603_X4 ROHS","0","4D03WGJ0103T5E","","","","","","","","","","","",""
"TS-1187A-B-A-B","S1","TS-1187A-B-A-B:TS1187ABAB","","C318884","","Tactile Switches SPST 5.10mm x 5.10mm 0.40mm 50mA @ 12VDC SMD RoHS","1","TS-1187A-B-A-B","4.05","https://lcsc.com/product-detail/Tactile-Switches_XKB-Enterpr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","XKB Enterprise","TS-1187A-B-A-B","","","","","","","",""
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

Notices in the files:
README.md:
License: AGPL v3
